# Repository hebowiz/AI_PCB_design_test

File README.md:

# AI PCB Design Test

AIによる回路・基板設計の実地検証プロジェクト（開始: 2026-11-19）。

## 3つの設計手段 × 2つの検証内容

**設計手段**
1. atopile + KiCad（配置・自動配線にFreerouting等を併用）
2. KiCad単独で回路図・PCBを直接作成・編集
3. EasyEDA Proで回路図・PCBを直接作成・編集

**検証内容**
- **A: 新規設計** — 1・2・3すべてで実施。同一の要求仕様を与え、結果と工程を比較する。
- **B: 既存KiCad設計の修正** — **2のみ**で実施。既存の人間設計を保護しながら変更する。

| 設計手段 | A: 新規設計 | B: 既存KiCad修正 |
| --- | --- | --- |
| 1. atopile + KiCad | A-1 | 対象外 |
| 2. KiCad | A-2 | B-2 |
| 3. EasyEDA Pro | A-3 | 対象外 |

検証ケースは合計4つ。詳しい評価項目は `docs/comparison_matrix.md`。

## KiCadで最新A-2を開く場所

**固定ローカルWorktree（ローカルCodexによる初回セットアップが必要）**

```text
<リポジトリ>/workspaces/A-2/01_New_Design/kicad_direct/a2_usb_uart.kicad_pro
```

`main/01_New_Design/kicad_direct/`にあるA-2回路図は初期設計であり、R-0016まで修正された最新版ではありません。固定Worktreeはリポジトリ内に作りますが、Gitの`workspaces/`をignoreするためGitHub上には表示されません。詳細は[固定ワークスペース運用](docs/design_workspaces.md)を参照。

## ディレクトリ
- `01_New_Design/specs/` — A-1/A-2/A-3に共通の要求仕様
- `01_New_Design/atopile/` — A-1の成果物
- `01_New_Design/kicad_direct/` — A-2の成果物
- `01_New_Design/easyeda/` — A-3の成果物
- `02_Design_Modification/` — B-2だけの作業（KiCad既存設計修正）
- `docs/` — 議論、決定、作業、ツール環境、評価

## スキル・出典

`.agents/skills/pcb-pipeline/` に [nobkat/auto-pcb-skill](https://github.com/nobkat/auto-pcb-skill) の `pcb-pipeline` スキルを、試験用に取り込んでいます（MIT License）。出典、取得リビジョン、ライセンスについては `THIRD_PARTY_NOTICES.md` を参照してください。

Codexからの利用: `$pcb-pipeline`。

回路図作図用の独立追加スキル：`.agents/skills/schematic-design/`（電気的同一性・品質確認）、`.agents/skills/schematic-style-standard/`（V3系の作図スタイル）。回路図を作成・修正する自然言語の指示で、共通スキルと標準スタイルを自動適用する（手動のスキル名指定は不要）。既存の`pcb-pipeline`を改変せず、別スタイルを将来追加できる構成。

**注意:** オリジナルはmacOS/Linux向け。Windows環境での実行可否・必要な変更は未検証。スキルを配置しただけではatopile/KiCad/Freerouting/Java等はインストールされません。

レビュー議事録の自動整理と品質チェックには、独立スキル[design-review-records](.agents/skills/design-review-records/SKILL.md)を適用します。回路設計・回路図・PCB・製造のレビュー台帳は共通で、変更履歴と技術的な判断を保持します。

## 記録と安全

- `AGENTS.md`: Codexの作業ルール
- `docs/discussion_log.md`: 議論・技術的仮説
- `docs/decision_log.md`: 決定と判断理由
- `docs/work_log.md`: 実施作業・結果・検証証跡
- `docs/report_outline.md`: 後日レポート化するための章立て
- [回路図・基板図の横並び比較（ユーザーレビュー前）](docs/initial_3way_review.md)
- [3方式の統合レポート](docs/design_integration_report.md)
- [将来構想：設計ノウハウを蓄積するAI設計エージェント（改訂前提）](docs/future_design_agent_vision.md)
- [A-2 V3-polish 回路図レビュー候補版の一次確認](docs/a2_schematic_v3_polish_assistant_review.md)

設計結果はERC/DRCだけで妥当と判断せず、部品・回路・RF/EMC・熱・製造性・実機動作を別途確認すること。

## 参考

- [検討の発端となった記事](https://note.com/energylab/n/nd24d482f28ca)
- [auto-pcb-skill](https://github.com/nobkat/auto-pcb-skill)

## EasyEDA Proの導入

A-3ではEasyEDA Proのデスクトップ版と公式CLI/Extension APIを使う。導入・確認方法は `docs/easyeda_setup.md`。使用ツールの導入状況と実際の動作検証は別に記録する。

- 公式: https://prodocs.easyeda.com/en/api/guide/cli.html
- AI向け手順: https://prodocs.easyeda.com/storage/texts/api/guide/cli-for-ai.md

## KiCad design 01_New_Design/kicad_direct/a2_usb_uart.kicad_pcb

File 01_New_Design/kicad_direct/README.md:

# A-2 KiCad直接設計

現在のブランチは承認済み回路図をPCBへ同期したレビュー候補版です。[PCB同期の結果・画像・未解決事項](reports/pcb_sync/README.md)を参照してください。回路図とPCBの整合性を検証済みですが、人間によるPCB承認は未実施です。BOM・Gerber・ドリル・実装座標は旧版のままです。

## 初回設計時の記録

FT232Hを使ったUSB-UART基板の製造前レビュー版。UART信号はTXD/RXD/RTS#/CTS#、外形は22 × 50 mm、板厚は1.6 mm、2層で、58部品をA面に配置した。

回路図、配置・配線済みPCB、部品表、Gerber、ドリル、実装座標を作成した。最終ERC/DRCは警告・エラーとも0件、未配線0件、回路図とPCBの不一致0件。ただしUSBの90 Ω差動配線とヘッダの正式ランド寸法が未確認のため、製造へリリースできる状態ではない。

|用途|ファイル|
|---|---|
|設計結果|[結果・未検証事項](reports/result.md)|
|経緯|[作業記録](reports/work_log.md)、[判断記録](reports/decision_log.md)、[検討記録](reports/discussion_log.md)|
|図面|[回路図PDF](reports/schematic.pdf)、[PCB各層PDF](reports/pcb_layers.pdf)|
|編集用CAD|[プロジェクト](a2_usb_uart.kicad_pro)、[回路図](a2_usb_uart.kicad_sch)、[PCB](a2_usb_uart.kicad_pcb)|
|製造出力|[レビュー用製造データ](manufacturing_review/README.md)|

KiCad 10.0.8で作成。atopileは使用せず、他方式の成果物も参照していない。設計データはローカルで生成した。製造業者へのアップロードや発注はしていない。

## 再検証と出力

PowerShellから、リポジトリのルートで実行する。

```powershell
& ./01_New_Design/kicad_direct/scripts/export.ps1
& "$env:LOCALAPPDATA/Programs/KiCad/10.0/bin/python.exe" ./01_New_Design/kicad_direct/scripts/verify.py
```

`export.ps1`はERC/DRCが通った場合に出力する。編集・再出力には保存済みの回路図・PCBを使う。`generate.py --replace-generated`は回路図とPCBを作り直して配線を失わせるため、通常の再出力には使わない。`route.py`、`repair_routes.py`、`resolve_cages.py`は今回の生成・修正過程の記録であり、完成PCBに順次実行する手順ではない。人手で変更した後は、差分とバックアップを確認せずに再生成・再配線しない。

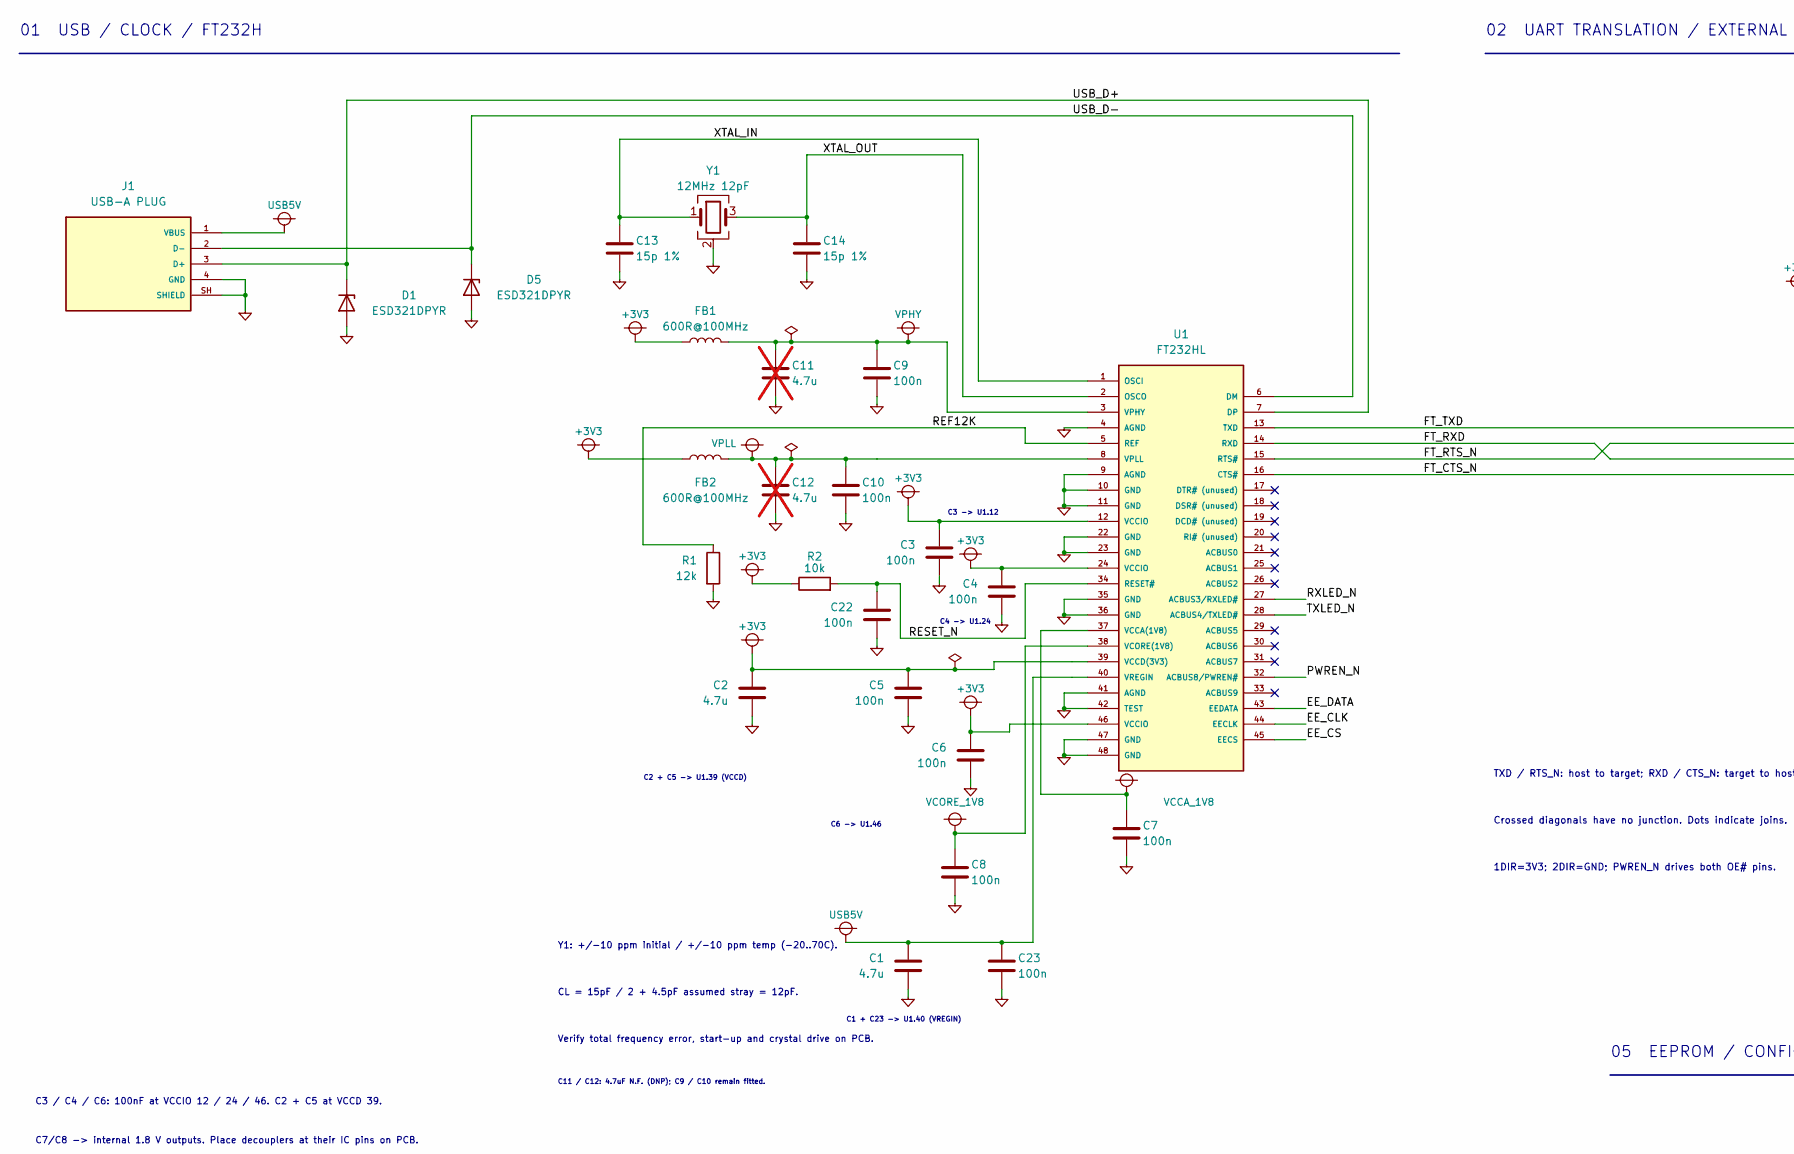
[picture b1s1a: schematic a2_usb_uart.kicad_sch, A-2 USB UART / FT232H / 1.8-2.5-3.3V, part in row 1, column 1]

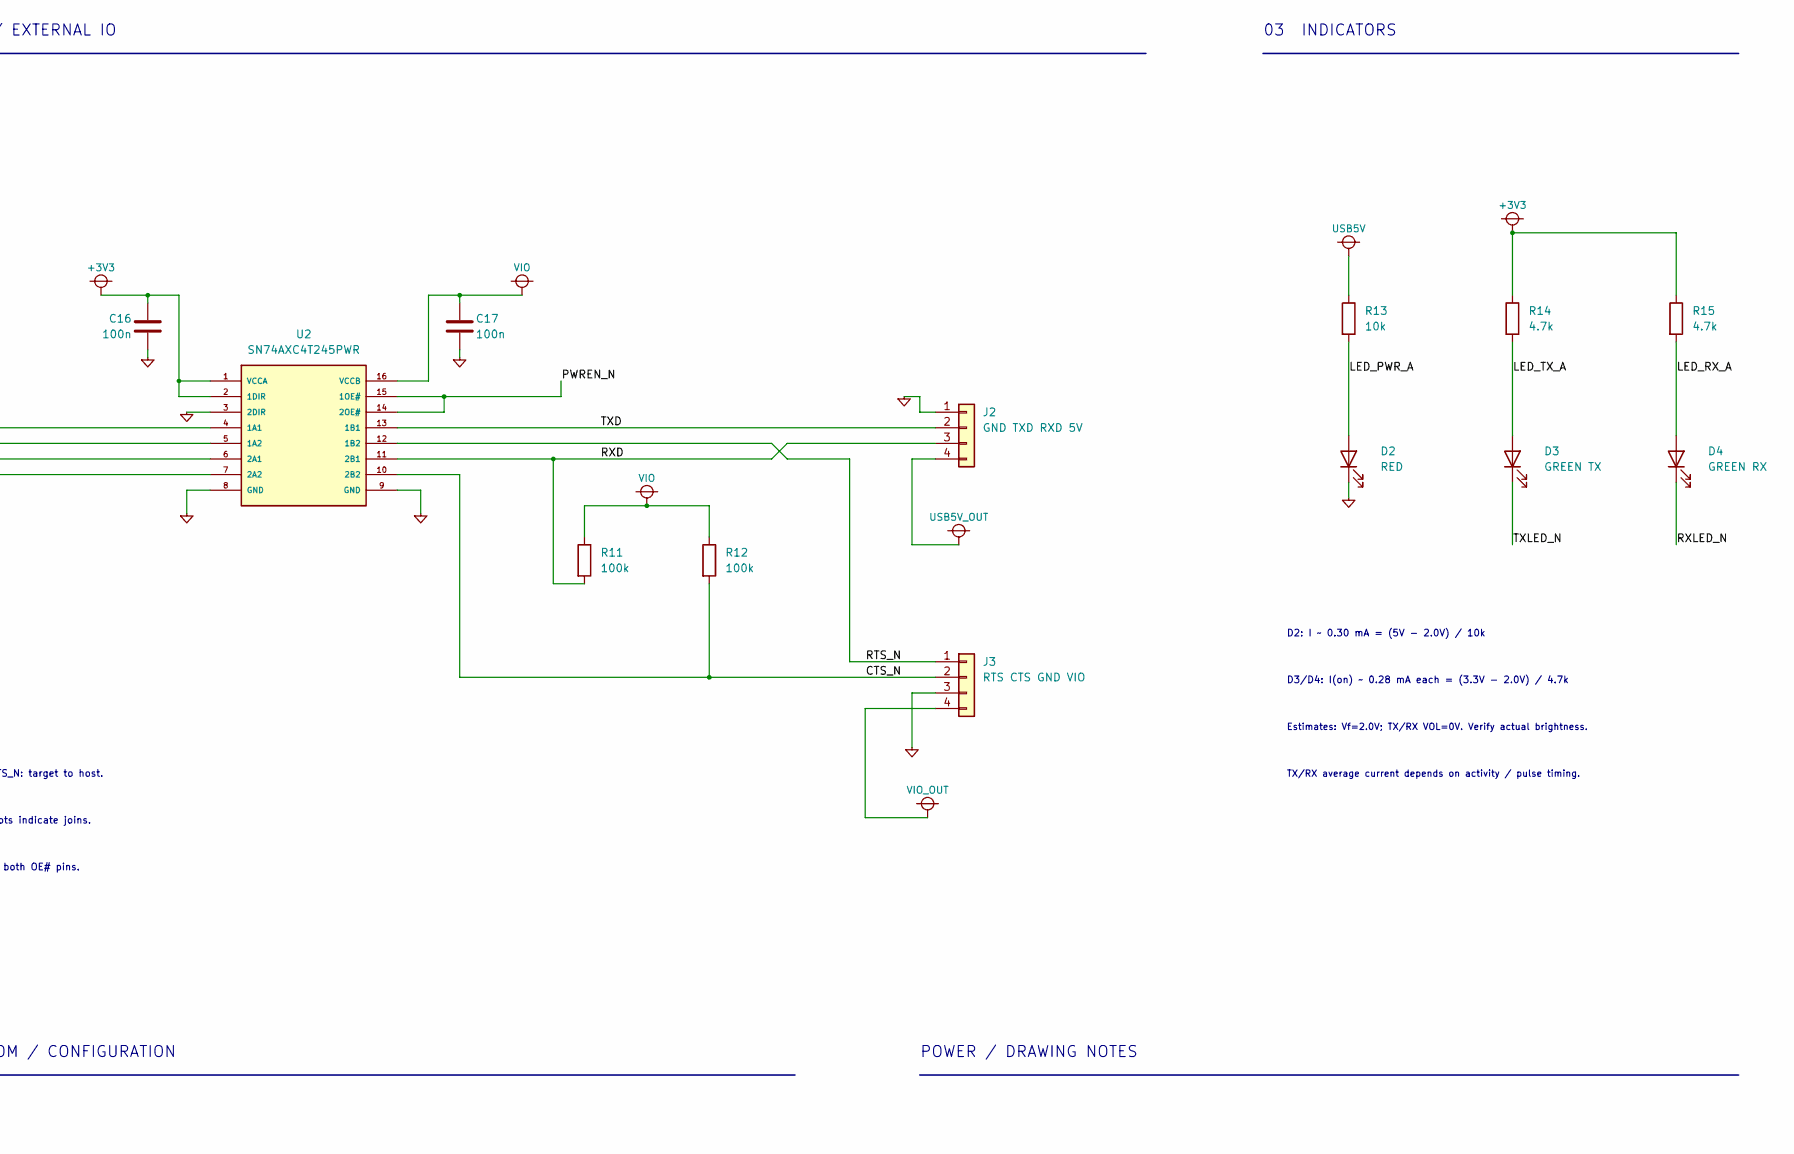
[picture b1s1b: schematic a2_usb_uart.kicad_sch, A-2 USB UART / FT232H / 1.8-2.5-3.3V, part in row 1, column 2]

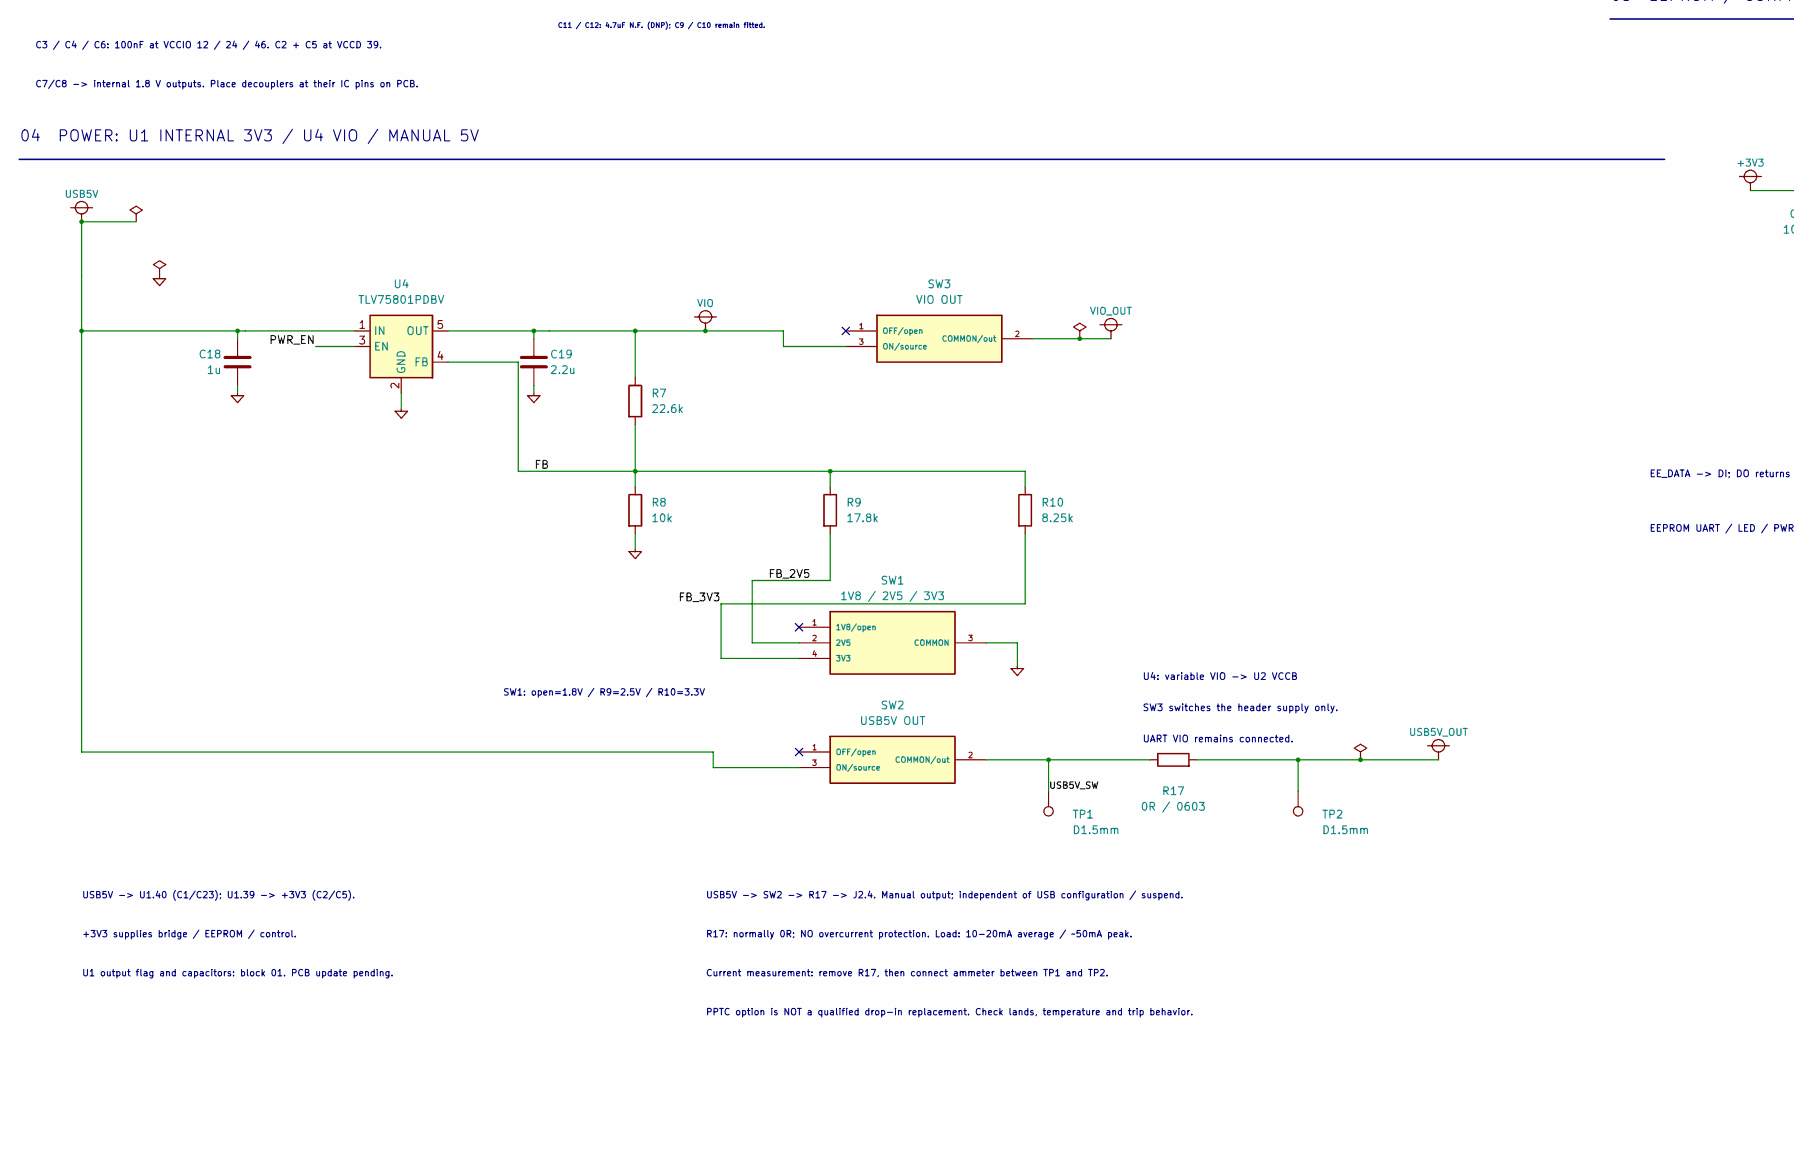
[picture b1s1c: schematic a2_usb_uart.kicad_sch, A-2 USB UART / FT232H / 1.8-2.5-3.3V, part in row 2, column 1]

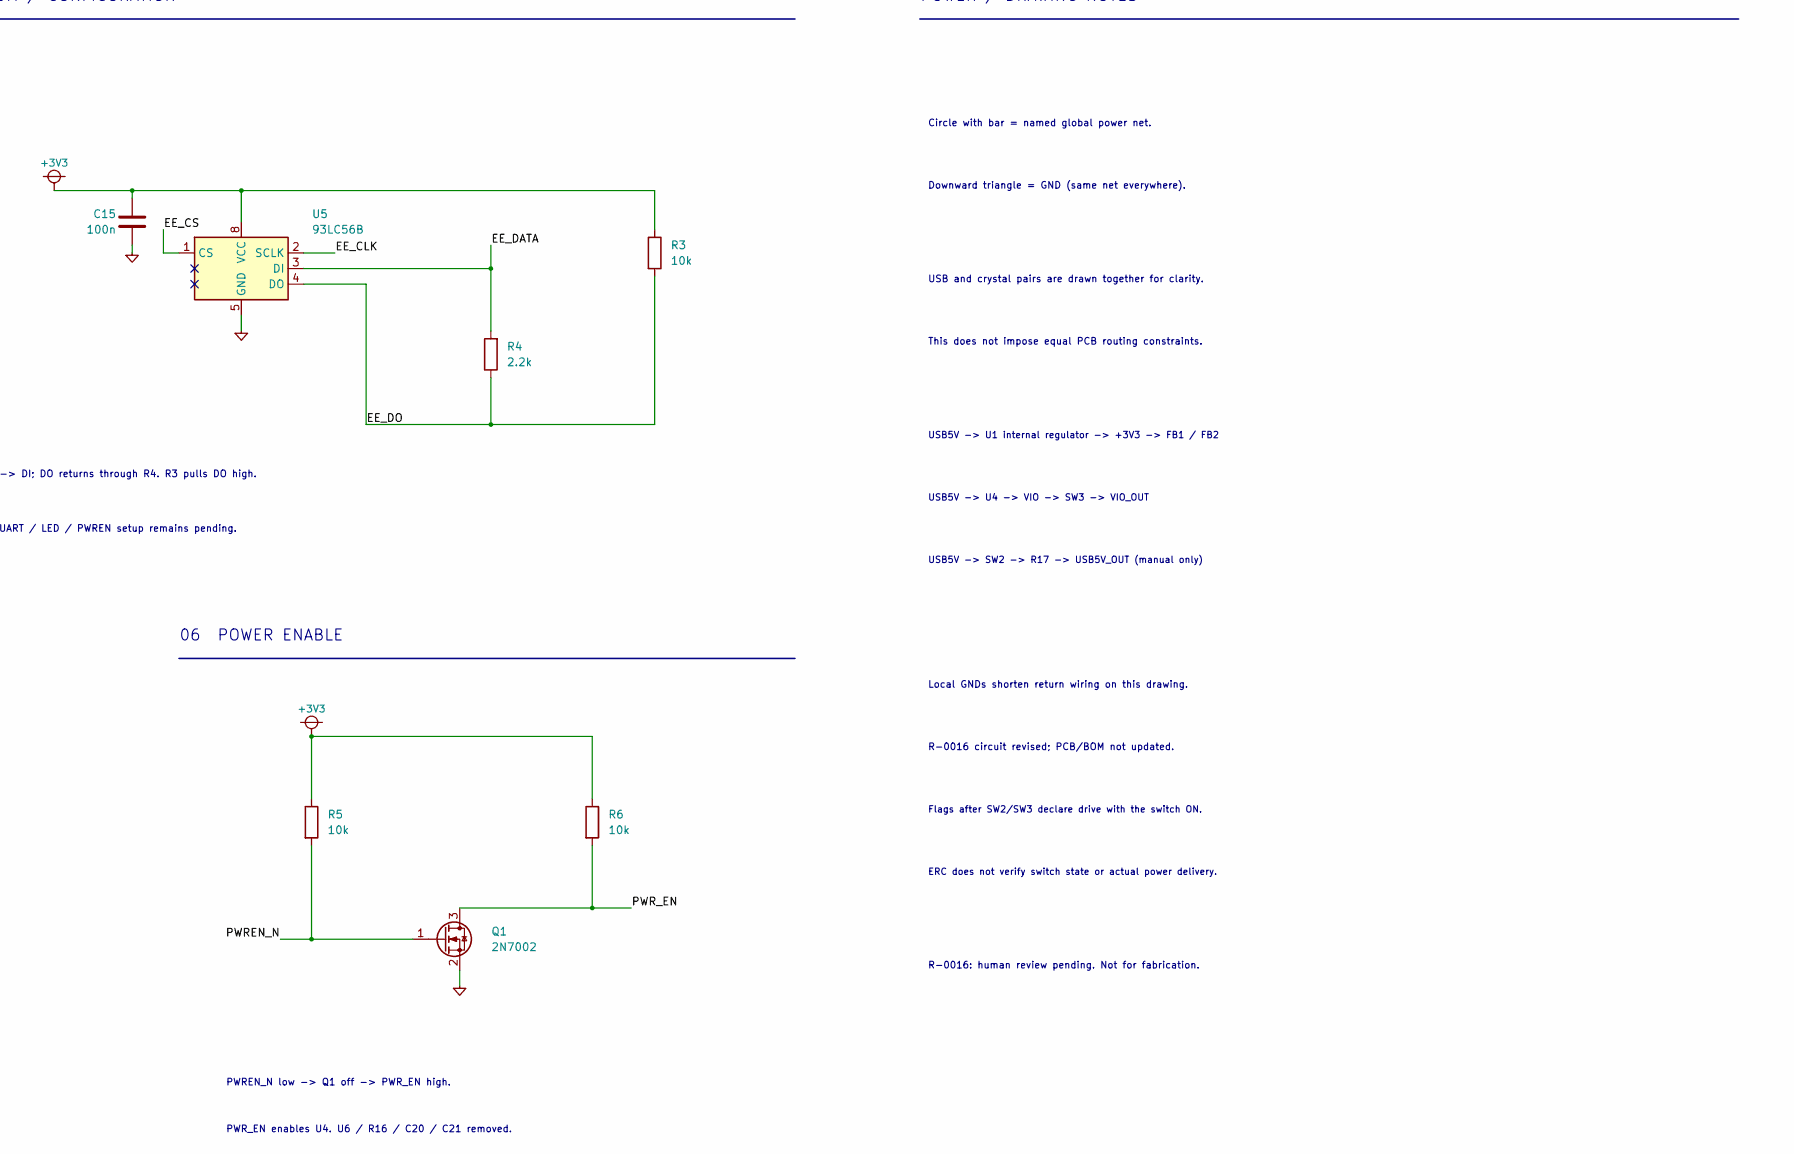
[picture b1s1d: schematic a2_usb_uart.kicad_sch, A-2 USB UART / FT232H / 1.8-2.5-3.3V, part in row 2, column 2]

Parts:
C1, C2: 4.7u; C_0805_2012Metric; MPN CL21A475KAQNNNE
C3, C4, C5, C6, C7, C8, C9, C10, C15, C16, C17, C22, C23: 100n; C_0402_1005Metric; MPN CL05B104KO5NNNC
C11, C12: 4.7u; C_0805_2012Metric; MPN CL21A475KAQNNNE; not fitted
C13, C14: 15p 1%; C_0402_1005Metric; MPN GRM1555C1H150FA01D
C18: 1u; C_0402_1005Metric; MPN CL05A105KA5NQNC
C19: 2.2u; C_0603_1608Metric; MPN GRM188R61A225KE34D
D1, D5: ESD321DPYR; Texas_DPY0002A_0.6x1mm_P0.65mm; MPN ESD321DPYR
D2: RED; LED_0603_1608Metric; MPN LTST-C190KRKT
D3: GREEN TX; LED_0603_1608Metric; MPN LTST-C190KGKT
D4: GREEN RX; LED_0603_1608Metric; MPN LTST-C190KGKT
FB1, FB2: 600R@100MHz; L_0402_1005Metric; MPN BLM15AG601SN1D
J1: USB-A PLUG; USB_A_Molex_48037-2200_Horizontal; MPN 0480372200
J2: GND TXD RXD 5V; TSM_104_SH_PROVISIONAL; MPN TSM-104-01-T-SH
J3: RTS CTS GND VIO; TSM_104_SV; MPN TSM-104-01-T-SV
Q1: 2N7002; SOT-23; MPN 2N7002P,215
R1: 12k; R_0402_1005Metric; MPN RC0402FR-0712KL
R2, R3, R5, R6, R8, R13: 10k; R_0402_1005Metric; MPN RC0402FR-0710KL
R4: 2.2k; R_0402_1005Metric; MPN RC0402FR-072K2L
R7: 22.6k; R_0402_1005Metric; MPN RC0402FR-0722K6L
R9: 17.8k; R_0402_1005Metric; MPN RC0402FR-0717K8L
R10: 8.25k; R_0402_1005Metric; MPN RC0402FR-078K25L
R11, R12: 100k; R_0402_1005Metric; MPN RC0402FR-07100KL
R14, R15: 4.7k; R_0402_1005Metric; MPN RC0402FR-074K7L
R17: 0R / 0603; R_0603_Bourns_CRPF; MPN CR0603-J/-000EPF
SW1: 1V8 / 2V5 / 3V3; SW_SP3T_PCM13; MPN PCM13SMTR
SW2: USB5V OUT; SW_SPDT_PCM12; MPN PCM12SMTR
SW3: VIO OUT; SW_SPDT_PCM12; MPN PCM12SMTR
TP1, TP2: D1.5mm; TestPoint_Pad_D1.5mm; MPN PCB copper pad; no fitted component
U1: FT232HL; LQFP-48_7x7mm_P0.5mm; MPN FT232HL-REEL
U2: SN74AXC4T245PWR; TSSOP-16_4.4x5mm_P0.65mm; MPN SN74AXC4T245PWR
U4: TLV75801PDBV; SOT-23-5; MPN TLV75801PDBVR
U5: 93LC56B; MSOP-8_3x3mm_P0.65mm; MPN 93LC56B-I/MS
Y1: 12MHz 12pF; Crystal_SMD_3225-4Pin_3.2x2.5mm; MPN ABM8-12.000MHZ-12-B1U-T

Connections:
+3V3: C2.1, C3.1, C4.1, C5.1, C6.1, C15.1, C16.1, FB1.1, FB2.1, R2.1, R3.1, R5.1, R6.1, R14.1, R15.1, U1.12 (VCCIO), U1.24 (VCCIO), U1.39 (VCCD(3V3)), U1.46 (VCCIO), U2.1 (VCCA), U2.2 (1DIR), U5.8 (VCC)
/CTS_N: J3.2, R12.2, U2.10 (2B2)
/EE_CLK: U1.44 (EECLK), U5.2 (SCLK)
/EE_CS: U1.45 (EECS), U5.1 (CS)
/EE_DATA: R4.2, U1.43 (EEDATA), U5.3 (DI)
/EE_DO: R3.2, R4.1, U5.4 (DO)
/FB: R7.2, R8.1, R9.1, R10.1, U4.4 (FB)
/FB_2V5: R9.2, SW1.2 (2V5)
/FB_3V3: R10.2, SW1.4 (3V3)
/FT_CTS_N: U1.16 (CTS#), U2.7 (2A2)
/FT_RTS_N: U1.15 (RTS#), U2.5 (1A2)
/FT_RXD: U1.14 (RXD), U2.6 (2A1)
/FT_TXD: U1.13 (TXD), U2.4 (1A1)
/LED_PWR_A: D2.2 (A), R13.2
/LED_RX_A: D4.2 (A), R15.2
/LED_TX_A: D3.2 (A), R14.2
/PWREN_N: Q1.1 (G), R5.2, U1.32 (ACBUS8/PWREN#), U2.14 (2OE#), U2.15 (1OE#)
/PWR_EN: Q1.3 (D), R6.2, U4.3 (EN)
/REF12K: R1.1, U1.5 (REF)
/RESET_N: C22.1, R2.2, U1.34 (RESET#)
/RTS_N: J3.1, U2.12 (1B2)
/RXD: J2.3, R11.2, U2.11 (2B1)
/RXLED_N: D4.1 (K), U1.27 (ACBUS3/RXLED#)
/TXD: J2.2, U2.13 (1B1)
/TXLED_N: D3.1 (K), U1.28 (ACBUS4/TXLED#)
/USB5V_SW: R17.1, SW2.2 (COMMON/out), TP1.1
/USB_D+: D1.1 (K), J1.3 (D+), U1.7 (DP)
/USB_D-: D5.1 (K), J1.2 (D-), U1.6 (DM)
/XTAL_IN: C13.1, U1.1 (OSCI), Y1.1
/XTAL_OUT: C14.1, U1.2 (OSCO), Y1.3
GND: C1.2, C2.2, C3.2, C4.2, C5.2, C6.2, C7.2, C8.2, C9.2, C10.2, C11.2, C12.2, C13.2, C14.2, C15.2, C16.2, C17.2, C18.2, C19.2, C22.2, C23.2, D1.2 (A), D2.1 (K), D5.2 (A), J1.4 (GND), J1.SH (SHIELD), J2.1, J3.3, Q1.2 (S), R1.2, R8.2, SW1.3 (COMMON), U1.4 (AGND), U1.9 (AGND), U1.10 (GND), U1.11 (GND), U1.22 (GND), U1.23 (GND), U1.35 (GND), U1.36 (GND), U1.41 (AGND), U1.42 (TEST), U1.47 (GND), U1.48 (GND), U2.3 (2DIR), U2.8 (GND), U2.9 (GND), U4.2 (GND), U5.5 (GND), Y1.2 (G), Y1.4 (G)
USB5V: C1.1, C18.1, C23.1, J1.1 (VBUS), R13.1, SW2.3 (ON/source), U1.40 (VREGIN), U4.1 (IN)
USB5V_OUT: J2.4, R17.2, TP2.1
VCCA_1V8: C7.1, U1.37 (VCCA(1V8))
VCORE_1V8: C8.1, U1.38 (VCORE(1V8))
VIO: C17.1, C19.1, R7.1, R11.1, R12.1, SW3.3 (ON/source), U2.16 (VCCB), U4.5 (OUT)
VIO_OUT: J3.4, SW3.2 (COMMON/out)
VPHY: C9.1, C11.1, FB1.2, U1.3 (VPHY)
VPLL: C10.1, C12.1, FB2.2, U1.8 (VPLL)

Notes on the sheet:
01 USB / CLOCK / FT232H
02 UART TRANSLATION / EXTERNAL IO
03 INDICATORS
C3 / C4 / C6: 100nF at VCCIO 12 / 24 / 46. C2 + C5 at VCCD 39.
C7/C8 -> internal 1.8 V outputs. Place decouplers at their IC pins on PCB.
TXD / RTS_N: host to target; RXD / CTS_N: target to host.
Crossed diagonals have no junction. Dots indicate joins.
1DIR=3V3; 2DIR=GND; PWREN_N drives both OE# pins.
D2: I ~ 0.30 mA = (5V - 2.0V) / 10k
D3/D4: I(on) ~ 0.28 mA each = (3.3V - 2.0V) / 4.7k
04 POWER: U1 INTERNAL 3V3 / U4 VIO / MANUAL 5V
USB5V -> U1.40 (C1/C23); U1.39 -> +3V3 (C2/C5).
+3V3 supplies bridge / EEPROM / control.
U4: variable VIO -> U2 VCCB
SW3 switches the header supply only.
UART VIO remains connected.
SW1: open=1.8V / R9=2.5V / R10=3.3V
USB5V -> SW2 -> R17 -> J2.4. Manual output; independent of USB configuration / suspend.
05 EEPROM / CONFIGURATION
EE_DATA -> DI; DO returns through R4. R3 pulls DO high.
EEPROM UART / LED / PWREN setup remains pending.
06 POWER ENABLE
PWREN_N low -> Q1 off -> PWR_EN high.
PWR_EN enables U4. U6 / R16 / C20 / C21 removed.
POWER / DRAWING NOTES
Circle with bar = named global power net.
Downward triangle = GND (same net everywhere).
USB and crystal pairs are drawn together for clarity.
This does not impose equal PCB routing constraints.
USB5V -> U1 internal regulator -> +3V3 -> FB1 / FB2
USB5V -> U4 -> VIO -> SW3 -> VIO_OUT
USB5V -> SW2 -> R17 -> USB5V_OUT (manual only)
Local GNDs shorten return wiring on this drawing.
R-0016 circuit revised; PCB/BOM not updated.
Flags after SW2/SW3 declare drive with the switch ON.
ERC does not verify switch state or actual power delivery.
R-0016: human review pending. Not for fabrication.
Estimates: Vf=2.0V; TX/RX VOL=0V. Verify actual brightness.
TX/RX average current depends on activity / pulse timing.
Y1: +/-10 ppm initial / +/-10 ppm temp (-20..70C).

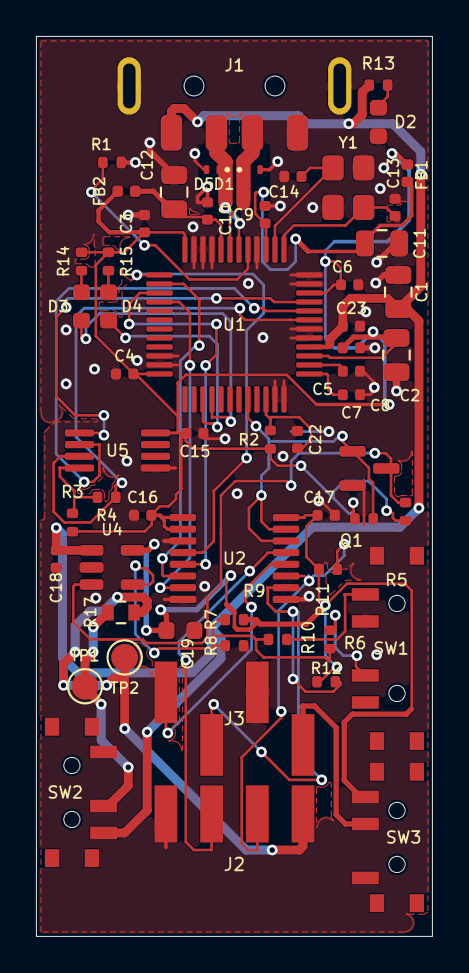
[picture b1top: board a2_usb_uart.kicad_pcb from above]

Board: 2 copper layers, 22.0 x 50.0 mm, 58 parts (0 on the bottom side), 39 nets.

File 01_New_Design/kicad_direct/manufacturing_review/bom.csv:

Reference,Value,MPN,Footprint,Notes
U1,FT232HL,FT232HL-REEL,Package_QFP:LQFP-48_7x7mm_P0.5mm,UART mode; EEPROM programming required
U2,SN74AXC4T245PWR,SN74AXC4T245PWR,Package_SO:TSSOP-16_4.4x5mm_P0.65mm,1DIR=1 (TX/RTS); 2DIR=0 (RX/CTS)
U3,AP2112K-3.3,AP2112K-3.3TRG1,Package_TO_SOT_SMD:SOT-23-5,Fixed bridge supply
U4,TLV75801PDBV,TLV75801PDBVR,Package_TO_SOT_SMD:SOT-23-5,1.8/2.5/3.3 V; change SW1 only while unpowered
U5,93LC56B,93LC56B-I/MS,Package_SO:MSOP-8_3x3mm_P0.65mm,16-bit organization
U6,TPS22919DCK,TPS22919DCKR,Package_TO_SOT_SMD:SOT-363_SC-70-6,USB external power disabled before enumeration / in suspend
Q1,2N7002,"2N7002P,215",Package_TO_SOT_SMD:SOT-23,Invert PWREN# for load switch and adjustable LDO
D1,TPD2EUSB30,TPD2EUSB30DRTR,Package_TO_SOT_SMD:Texas_DRT-3,USB ESD
J1,USB-A PLUG,0480372200,Connector_USB:USB_A_Molex_48037-2200_Horizontal,Vendor recommended 1.6 mm PCB adopted; mechanical fit requires prototype check
J2,GND TXD RXD 5V,TSM-104-01-T-SH,A2:TSM_104_SH_PROVISIONAL,PROVISIONAL footprint; manufacturer land-pattern confirmation required
J3,RTS CTS GND VIO,TSM-104-01-T-SV,Connector_PinHeader_2.54mm:PinHeader_1x04_P2.54mm_Vertical_SMD_Pin1Left,Generic KiCad land pattern; confirm exact part before fab
SW1,1V8 / 2V5 / 3V3,PCM13SMTR,Button_Switch_SMD:SW_SP3T_PCM13,"Common pin 3; pos1=1-3, pos2=2-3, pos3=3-4"
SW2,USB5V OUT,PCM12SMTR,Button_Switch_SMD:SW_SPDT_PCM12,Off/open or on; no external back-feed permitted
SW3,VIO OUT,PCM12SMTR,Button_Switch_SMD:SW_SPDT_PCM12,Switches header supply only; UART remains enabled
Y1,12MHz 18pF,ABM8-12.000MHZ-B2-T,Crystal:Crystal_SMD_3225-4Pin_3.2x2.5mm,27 pF loads assume 4.5 pF stray; frequency/start-up requires measurement
R1,12k,RC0402FR-0712KL,Resistor_SMD:R_0402_1005Metric,
R2,10k,RC0402FR-0710KL,Resistor_SMD:R_0402_1005Metric,
R3,10k,RC0402FR-0710KL,Resistor_SMD:R_0402_1005Metric,
R4,2.2k,RC0402FR-072K2L,Resistor_SMD:R_0402_1005Metric,
R5,10k,RC0402FR-0710KL,Resistor_SMD:R_0402_1005Metric,
R6,10k,RC0402FR-0710KL,Resistor_SMD:R_0402_1005Metric,
R7,22.6k,RC0402FR-0722K6L,Resistor_SMD:R_0402_1005Metric,
R8,10k,RC0402FR-0710KL,Resistor_SMD:R_0402_1005Metric,
R9,17.8k,RC0402FR-0717K8L,Resistor_SMD:R_0402_1005Metric,
R10,8.25k,RC0402FR-078K25L,Resistor_SMD:R_0402_1005Metric,
R11,100k,RC0402FR-07100KL,Resistor_SMD:R_0402_1005Metric,
R12,100k,RC0402FR-07100KL,Resistor_SMD:R_0402_1005Metric,
R13,10k,RC0402FR-0710KL,Resistor_SMD:R_0402_1005Metric,About 0.3 mA red indicator
R14,4.7k,RC0402FR-074K7L,Resistor_SMD:R_0402_1005Metric,About 0.28 mA green indicator
R15,4.7k,RC0402FR-074K7L,Resistor_SMD:R_0402_1005Metric,About 0.28 mA green indicator
R16,100,RC0402FR-07100RL,Resistor_SMD:R_0402_1005Metric,Discharge resistor
D2,RED,LTST-C190KRKT,LED_SMD:LED_0603_1608Metric,1608M; visual brightness unverified
D3,GREEN TX,LTST-C190KGKT,LED_SMD:LED_0603_1608Metric,1608M; visual brightness unverified
D4,GREEN RX,LTST-C190KGKT,LED_SMD:LED_0603_1608Metric,1608M; visual brightness unverified
C1,1u,CL05A105KA5NQNC,Capacitor_SMD:C_0402_1005Metric,Capacitance at DC bias must meet regulator minimum
C2,2.2u,GRM188R61A225KE34D,Capacitor_SMD:C_0603_1608Metric,Capacitance at DC bias must meet regulator minimum
C3,100n,CL05B104KO5NNNC,Capacitor_SMD:C_0402_1005Metric,Capacitance at DC bias must meet regulator minimum
C4,100n,CL05B104KO5NNNC,Capacitor_SMD:C_0402_1005Metric,Capacitance at DC bias must meet regulator minimum
C5,100n,CL05B104KO5NNNC,Capacitor_SMD:C_0402_1005Metric,Capacitance at DC bias must meet regulator minimum
C6,100n,CL05B104KO5NNNC,Capacitor_SMD:C_0402_1005Metric,Capacitance at DC bias must meet regulator minimum
C7,100n,CL05B104KO5NNNC,Capacitor_SMD:C_0402_1005Metric,Capacitance at DC bias must meet regulator minimum
C8,100n,CL05B104KO5NNNC,Capacitor_SMD:C_0402_1005Metric,Capacitance at DC bias must meet regulator minimum
C9,100n,CL05B104KO5NNNC,Capacitor_SMD:C_0402_1005Metric,Capacitance at DC bias must meet regulator minimum
C10,100n,CL05B104KO5NNNC,Capacitor_SMD:C_0402_1005Metric,Capacitance at DC bias must meet regulator minimum
C11,1u,CL05A105KA5NQNC,Capacitor_SMD:C_0402_1005Metric,Capacitance at DC bias must meet regulator minimum
C12,1u,CL05A105KA5NQNC,Capacitor_SMD:C_0402_1005Metric,Capacitance at DC bias must meet regulator minimum
C13,27p,C1005C0G1H270J050BA,Capacitor_SMD:C_0402_1005Metric,Capacitance at DC bias must meet regulator minimum
C14,27p,C1005C0G1H270J050BA,Capacitor_SMD:C_0402_1005Metric,Capacitance at DC bias must meet regulator minimum
C15,100n,CL05B104KO5NNNC,Capacitor_SMD:C_0402_1005Metric,Capacitance at DC bias must meet regulator minimum
C16,100n,CL05B104KO5NNNC,Capacitor_SMD:C_0402_1005Metric,Capacitance at DC bias must meet regulator minimum
C17,100n,CL05B104KO5NNNC,Capacitor_SMD:C_0402_1005Metric,Capacitance at DC bias must meet regulator minimum
C18,1u,CL05A105KA5NQNC,Capacitor_SMD:C_0402_1005Metric,Capacitance at DC bias must meet regulator minimum
C19,2.2u,GRM188R61A225KE34D,Capacitor_SMD:C_0603_1608Metric,Capacitance at DC bias must meet regulator minimum
C20,1u,CL05A105KA5NQNC,Capacitor_SMD:C_0402_1005Metric,Capacitance at DC bias must meet regulator minimum
C21,1u,CL05A105KA5NQNC,Capacitor_SMD:C_0402_1005Metric,Capacitance at DC bias must meet regulator minimum
C22,100n,CL05B104KO5NNNC,Capacitor_SMD:C_0402_1005Metric,Capacitance at DC bias must meet regulator minimum
FB1,600R@100MHz,BLM15AG601SN1D,Inductor_SMD:L_0402_1005Metric,Local PHY / PLL filtering
FB2,600R@100MHz,BLM15AG601SN1D,Inductor_SMD:L_0402_1005Metric,Local PHY / PLL filtering
